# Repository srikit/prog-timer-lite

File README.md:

# Programmable Timer Module

Programmable timer lite is a miniature, USB programmable timer module. This module can handle more than 100 alarm configurations and trigger the output channel based on the programmed conditions. The timer module can program using SRIKit's [*Timer Controller*](https://github.com/srikit/timer-controller) software. 

This module is designed around the *STM8S001J3M* microcontroller and *DS3231* real-time clock. *AMS1117-3.3* regulator in this module can handle a maximum of 9V DC input without installing an external heatsink. 

The alarm terminal of this module is available as an open-collector output. 

This module is specifically developed to handle long-duration alarm configurations which can span up to years. 

This is an open-source hardware project. All the design files, [documentation](https://github.com/srikit/prog-timer-lite/wiki), and firmware source code are available to download at the project source repository. Content of this project is distributed under the terms of the following license:

- Hardware License: [CERN-OHL-W](https://opensource.org/CERN-OHL-W)
- Software License: [GNU GPL 3.0](https://github.com/srikit/prog-timer-lite/blob/main/LICENSE)
- Documentation License: [CC BY 4.0](https://creativecommons.org/licenses/by/4.0)

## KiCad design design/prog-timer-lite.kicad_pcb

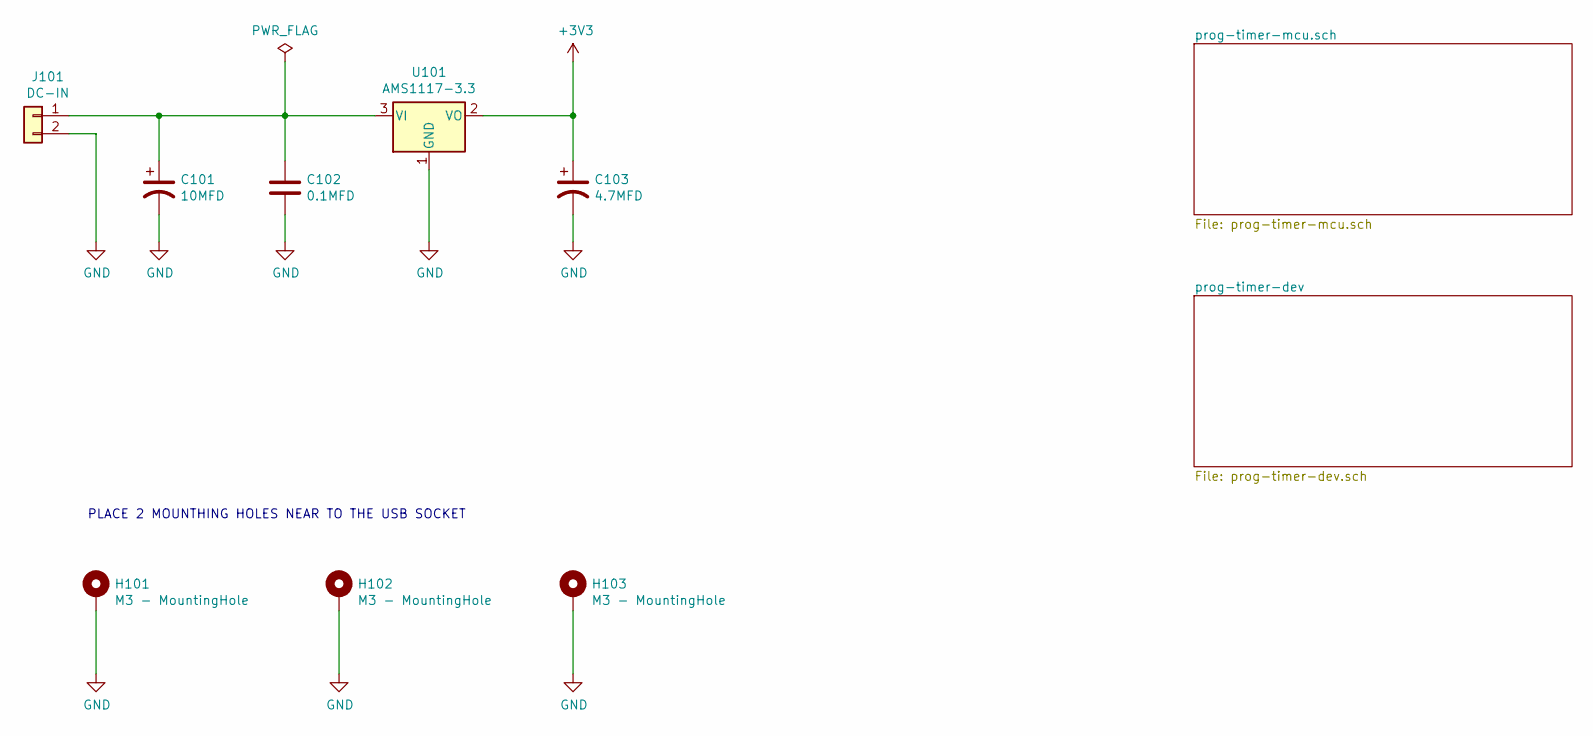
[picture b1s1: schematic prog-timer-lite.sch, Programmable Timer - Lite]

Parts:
C101: 10MFD; CP_Radial_D5.0mm_P2.50mm
C102: 0.1MFD; C_0805_2012Metric_Pad1.15x1.40mm_HandSolder
C103: 4.7MFD; CP_Radial_D5.0mm_P2.50mm
H101, H102, H103: M3 - MountingHole; MountingHole_3mm_Pad
J101: DC-IN; PhoenixContact_MCV_1,5_2-G-3.5_1x02_P3.50mm_Vertical
U101: AMS1117-3.3; SOT-223-3_TabPin2

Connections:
+3V3: C103.1, U101.2 (VO); also elsewhere on the board
GND: C101.2, C102.2, C103.2, H101.1, H102.1, H103.1, J101.2, U101.1 (GND); also elsewhere on the board
unnamed: C101.1, C102.1, J101.1, U101.3 (VI)

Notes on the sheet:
PLACE 2 MOUNTHING HOLES NEAR TO THE USB SOCKET

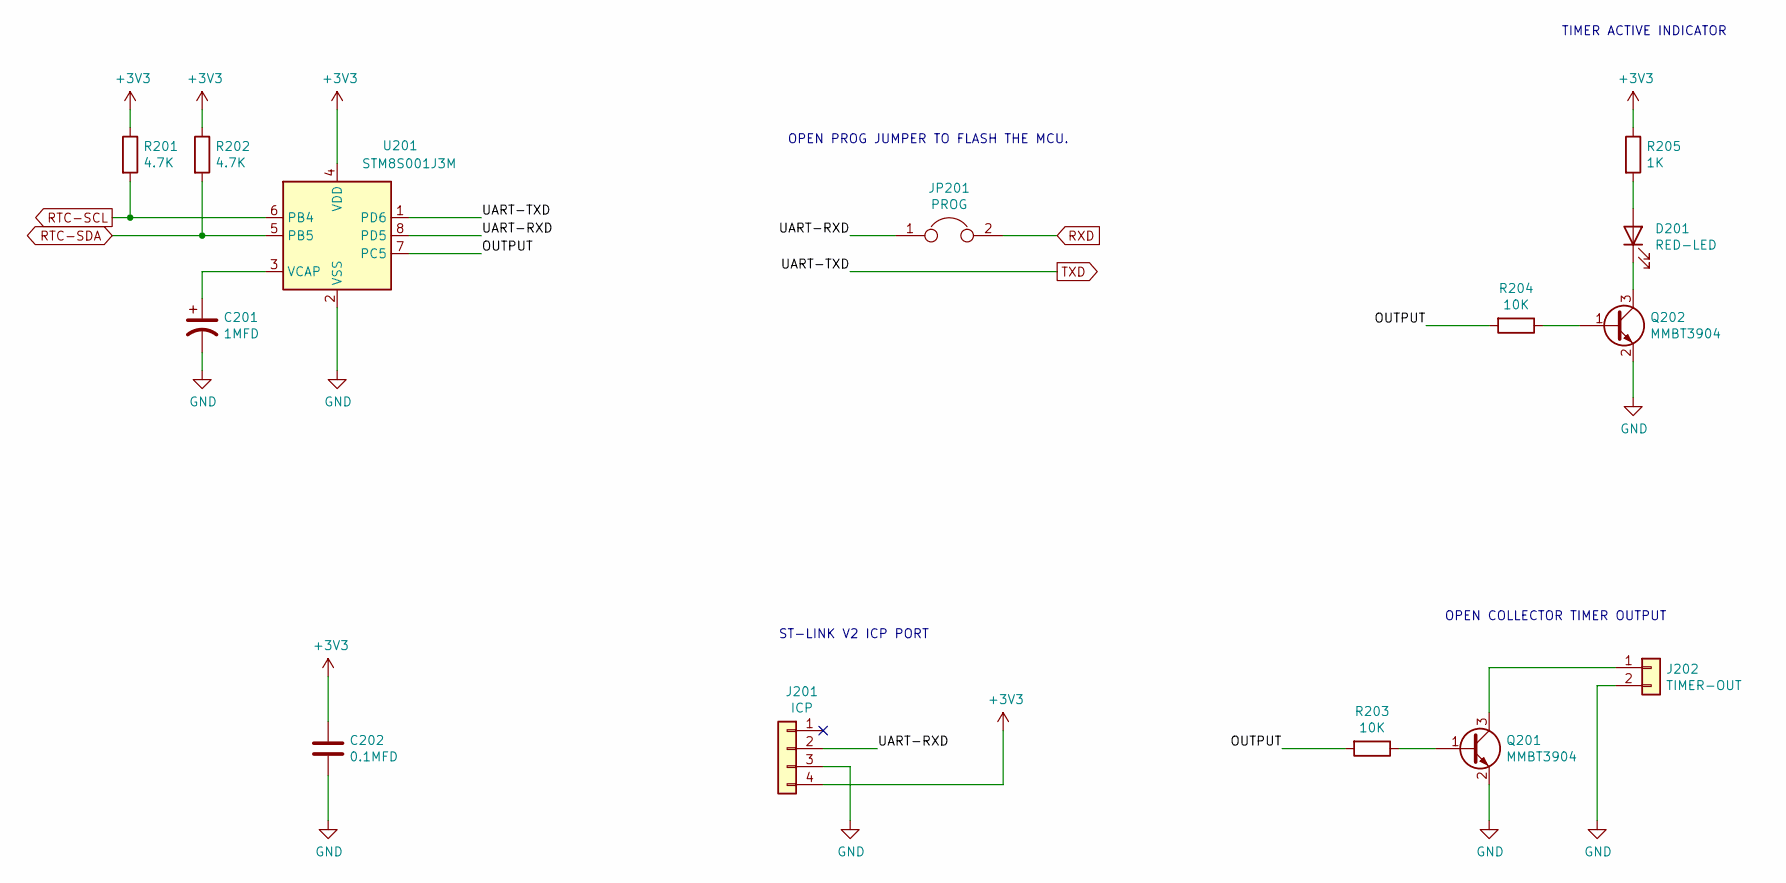
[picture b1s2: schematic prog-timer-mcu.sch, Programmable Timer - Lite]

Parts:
C201: 1MFD; C_0805_2012Metric_Pad1.15x1.40mm_HandSolder
C202: 0.1MFD; C_0805_2012Metric_Pad1.15x1.40mm_HandSolder
D201: RED-LED; LED_0805_2012Metric_Pad1.15x1.40mm_HandSolder
J201: ICP; pogo-2.54mmx4
J202: TIMER-OUT; PinHeader_1x02_P2.54mm_Vertical
JP201: PROG; SolderJumper-2_P1.3mm_Bridged_Pad1.0x1.5mm
Q201, Q202: MMBT3904; SOT-23
R201, R202: 4.7K; R_0805_2012Metric_Pad1.15x1.40mm_HandSolder
R203, R204: 10K; R_0805_2012Metric_Pad1.15x1.40mm_HandSolder
R205: 1K; R_0805_2012Metric_Pad1.15x1.40mm_HandSolder
U201: STM8S001J3M; SO-8_3.9x4.9mm_P1.27mm

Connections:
+3V3: C202.1, J201.4, R201.1, R202.1, R205.1, U201.4 (VDD); also elsewhere on the board
/prog-timer-mcu.sch/OUTPUT: R203.2, R204.2, U201.7 (PC5)
/prog-timer-mcu.sch/UART-RXD: J201.2, JP201.1, U201.8 (PD5)
GND: C201.2, C202.2, J201.3, J202.2, Q201.2 (E), Q202.2 (E), U201.2 (VSS); also elsewhere on the board
unnamed: C201.1, U201.3 (VCAP)
unnamed: D201.1 (K), Q202.3 (C)
unnamed: D201.2 (A), R205.2
unnamed: J202.1, Q201.3 (C)
unnamed: Q201.1 (B), R203.1
unnamed: Q202.1 (B), R204.1
RTC-SCL: R201.2, U201.6 (PB4); also elsewhere on the board
RTC-SDA: R202.2, U201.5 (PB5); also elsewhere on the board
RXD: JP201.2; also elsewhere on the board
TXD: U201.1 (PD6); also elsewhere on the board

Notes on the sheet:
OPEN PROG JUMPER TO FLASH THE MCU.
TIMER ACTIVE INDICATOR
ST-LINK V2 ICP PORT
OPEN COLLECTOR TIMER OUTPUT

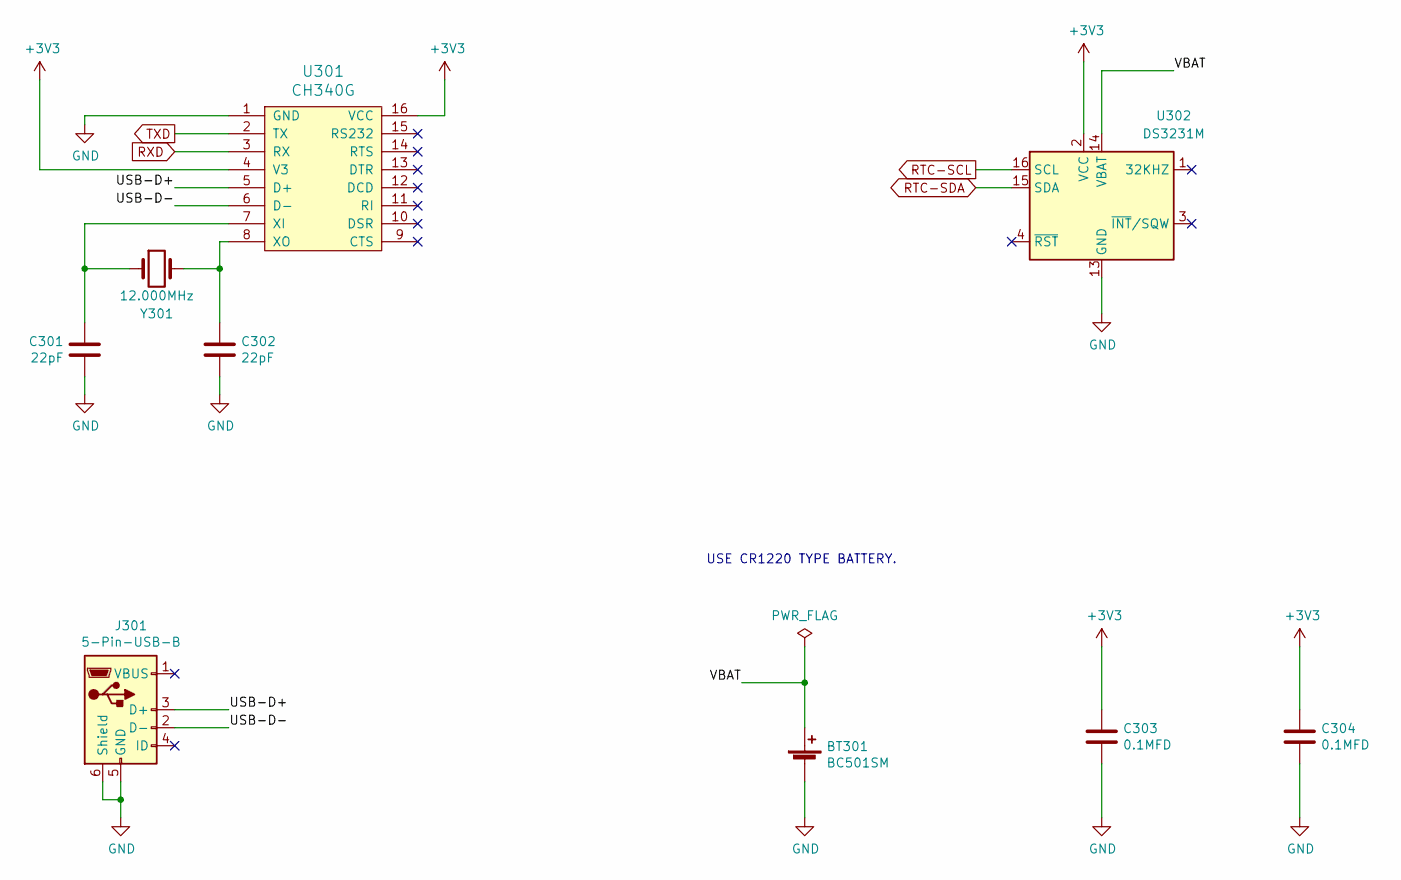
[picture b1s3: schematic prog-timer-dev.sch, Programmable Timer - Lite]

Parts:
BT301: BC501SM; MPD_BC501SM-TR
C301, C302: 22pF; C_0805_2012Metric_Pad1.15x1.40mm_HandSolder
C303, C304: 0.1MFD; C_0805_2012Metric_Pad1.15x1.40mm_HandSolder
J301: 5-Pin-USB-B; USB_Mini-B_Wuerth_65100516121_Horizontal
U301: CH340G; SOP-16_4.55x10.3mm_P1.27mm
U302: DS3231M; SOIC-16W_7.5x10.3mm_P1.27mm
Y301: 12.000MHz; Crystal_HC49-U_Vertical

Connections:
+3V3: C303.1, C304.1, U301.4 (V3), U301.16 (VCC), U302.2 (VCC); also elsewhere on the board
/prog-timer-dev/USB-D+: J301.3 (D+), U301.5 (D+)
/prog-timer-dev/USB-D-: J301.2 (D-), U301.6 (D-)
/prog-timer-dev/VBAT: BT301.1 (+), U302.14 (VBAT)
GND: BT301.2 (-), C301.1, C302.2, C303.2, C304.2, J301.5 (GND), J301.6 (Shield), U301.1 (GND), U302.5 (GND), U302.6 (GND), U302.7 (GND), U302.8 (GND), U302.9 (GND), U302.10 (GND), U302.11 (GND), U302.12 (GND), U302.13 (GND); also elsewhere on the board
unnamed: C301.2, U301.7 (XI), Y301.1
unnamed: C302.1, U301.8 (XO), Y301.2
RTC-SCL: U302.16 (SCL); also elsewhere on the board
RTC-SDA: U302.15 (SDA); also elsewhere on the board
RXD: U301.3 (RX); also elsewhere on the board
TXD: U301.2 (TX); also elsewhere on the board

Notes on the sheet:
USE CR1220 TYPE BATTERY.

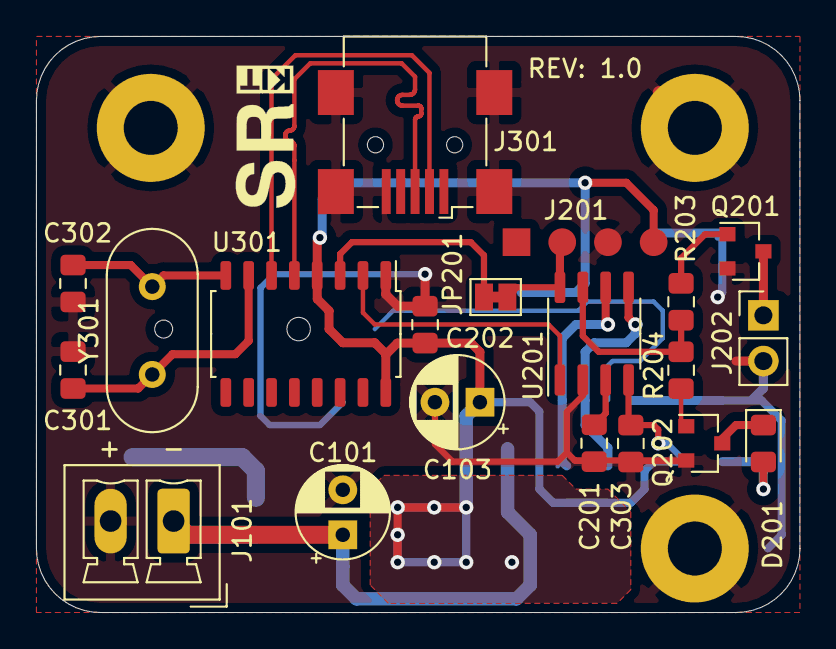
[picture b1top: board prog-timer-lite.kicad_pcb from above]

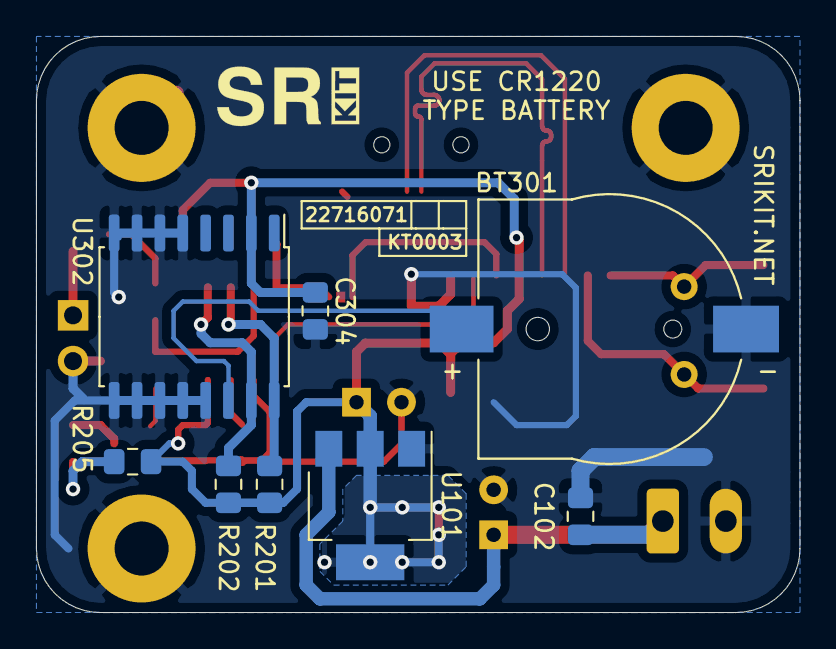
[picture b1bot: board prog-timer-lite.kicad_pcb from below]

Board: 2 copper layers, 42.4 x 32.0 mm, 31 parts (8 on the bottom side), 20 nets.

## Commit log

2021-05-19 Initial version of programmable timer module firmware and design files.
2021-05-19 Add link to Timer Programmer Git repository.
2021-05-21 Update link description of the Timer Controller.
2021-05-22 Add graphics, fritzing packages and CAD drawing of the module.
2021-05-22 Remove temporary design files from the repository.
2021-05-22 Add image of the PCB to the readme.md file.
2021-05-22 Add project ID into the readme.md file.
2021-05-22 Add Fritzing diagram for test setup.
2021-05-22 Add wiki link to the readme.md file.
2021-05-22 Add PDF version of the schematic diagram.
2021-05-22 Rename heading of the readme.md file.
